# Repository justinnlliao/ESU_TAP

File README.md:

# ESU-TAP: Foot Pedal Interface (micro-ROS)

ESU-TAP is a research PCB interposer between an electrosurgical generator and its
footswitch. It logs pedal presses and lets a computer close the same footswitch
contacts over ROS 2, while the surgeon's pedal keeps working. It does not carry
the RF/patient output.

> **Research prototype. Not validated for clinical use.** Board-power loss is
> intended to fall back to the manual pedal, but this is not a verified fail-safe
> or emergency stop. Read [Safety and validation](docs/SAFETY.md)
> before connecting a generator, and test on a generator-disconnected fixture first.

## What you need

- An assembled ESU-TAP board ([hardware](hardware/README.md): v1, v2 or v3) with an ESP32-DevKitC
- Regulated 5 V DC, center-positive barrel supply for the relay rail; USB for the ESP32
- Ubuntu 22.04 with ROS 2 Humble and Docker (Docker runs only the micro-ROS agent)

## Quick start

```bash
git clone <this repo> && cd ESU_TAP
./esu.sh setup              # once: PlatformIO + ROS package; asks whether to pull the Docker agent
./esu.sh flash v3 pedal     # ESP32 plugged in, generator DISCONNECTED (v1/v2/v3; pedal or nopedal)
./esu.sh run                # agent + logger + commander in one tmux window
```

In the commander type `arm`, then `c`/`g`/`b`/`l` (cut/coag/bipolar/LigaSure),
`x` = all OFF and disarm, `q` = quit. `./esu.sh stop` stops everything.
`./esu.sh run v3 T01` also passes a trial ID to the logger.
`./esu.sh update` pulls, rebuilds and offers to reflash; `./esu.sh help` lists
everything. If `./esu.sh` says permission denied, use `bash esu.sh`.

- **pedal** (normal): boots in manual, with the pedal forwarded and logged.
  `/esu/arm` switches to autonomous (ROS drives the relays). Pressing any pedal
  cancels all computer commands and hands control back; re-arm to resume.
- **nopedal**: only for boards with nothing wired to the pedal inputs.

## Using ESU-TAP from your own ROS 2 nodes

Once flashed, only the micro-ROS agent has to run (`./esu.sh agent`). The board
then appears as ordinary services and a topic on `ROS_DOMAIN_ID` 0; no package
from this repository is needed.

| Interface | Type | Purpose |
| --- | --- | --- |
| `/esu/arm` | `std_srvs/srv/SetBool` | Enable/disable computer control (pedals always work) |
| `/esu/cut`, `/esu/coag`, `/esu/bipolar` | `std_srvs/srv/SetBool` | Set/clear a channel |
| `/esu/ligasure` | `std_srvs/srv/SetBool` | Set/clear LigaSure (v3 only) |
| `/esu/capabilities` | `std_srvs/srv/Trigger` | JSON: board, channels, firmware, armed state |
| `/esu/activation_state` | `std_msgs/msg/Int32` | Packed current state, published on change |

```bash
ros2 service call /esu/arm std_srvs/srv/SetBool "{data: true}"
ros2 service call /esu/cut std_srvs/srv/SetBool "{data: true}"
ros2 topic echo /esu/activation_state
```

A computer ON command expires after 500 ms: re-send ON about every 100 ms while
the channel should stay on. Only one node should send commands at a time.

`activation_state` bits 0-3 are CUT, COAG, bipolar, LigaSure; bits 4-5 are the
source: 0 pedal, 1 computer, 2 boot/reconnect baseline, 3 takeover (a pedal
press ended computer control; sent with the released computer channel, or with
the unchanged state when no computer output had to open).

To record data alongside your node, run `./esu.sh logger v3 <trial-id>`. It
writes `~/pedal_logs/pedal_log_<trial-id>_<time>.csv` plus a `.metadata.jsonl`.

### Package in another workspace

`software/ros2/src/pedal_controller` can be copied alone into another
workspace's `src/` and built with colcon; it depends only on `rclpy`,
`std_msgs` and `std_srvs`. From that workspace,
`bash src/pedal_controller/esu_run.sh v3` starts the agent, logger and commander.
See [setup](docs/SETUP.md#5-package-in-another-ros-2-workspace).

## How it works

Bypass relays route the pedal contacts to ESP32 inputs. The firmware closes
separate activation relays on the generator side when either a pedal is pressed
or an armed computer command is active. With board power off, the relays fall
back to connecting the pedal straight to the generator. Published state is
inferred from inputs and commands, not measured contact closure or RF delivery.

## Documentation

- [Setup guide](docs/SETUP.md): build, flash, run, logs
- [Safety and validation](docs/SAFETY.md): protections, known gaps, test record
- [Hardware](hardware/README.md) and [connectors](docs/CONNECTORS.md)
- [Changelog](CHANGELOG.md)

For contributors: [CONTRIBUTING.md](CONTRIBUTING.md) and
[docs/contributors/](docs/contributors/README.md) (testing, roadmap, firmware
internals, hardware proposals, enclosure).

## License

[Apache 2.0](LICENSE).

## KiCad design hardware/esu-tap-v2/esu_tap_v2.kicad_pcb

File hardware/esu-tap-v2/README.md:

# ESU-TAP v2

Six-relay, three-channel (CUT, COAG, bipolar) design. Open `esu_tap_v2.kicad_pro`.
Build firmware with `--board v2`.

One v2 board passed a disconnected-fixture bench session on 2026-10-22; see the
[test record](../../docs/SAFETY.md#recorded-v2-disconnected-fixture-test-2026-10-22).
U9 RESET drives Q1 (bypass relays only) and ESP32 EN is unconnected, so the
watchdog does not reset the ESP32 or clear activation outputs.

Enclosure dimensions: [contributors/ENCLOSURE_V2.md](../../docs/contributors/ENCLOSURE_V2.md).
The v3 reference designators in
[HARDWARE_FAULT_HANDLING.md](../../docs/contributors/HARDWARE_FAULT_HANDLING.md)
do not apply directly to v2.

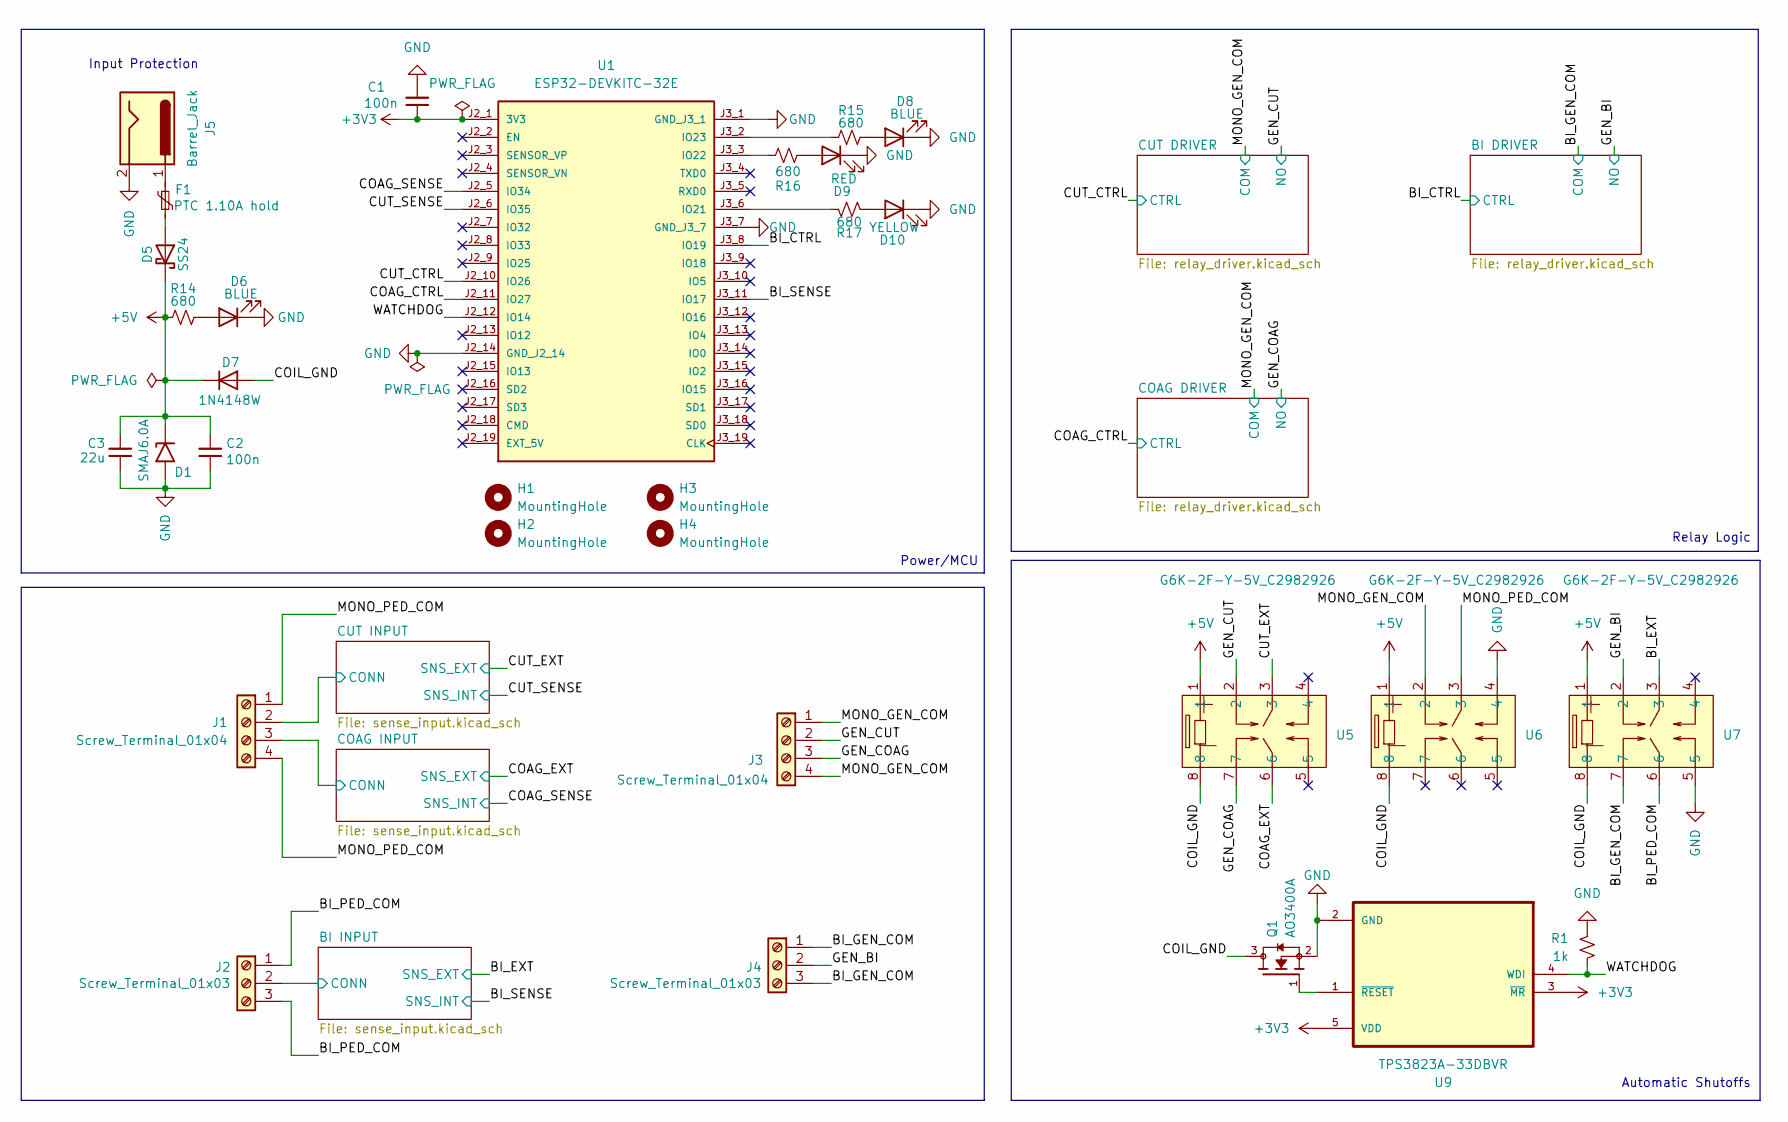
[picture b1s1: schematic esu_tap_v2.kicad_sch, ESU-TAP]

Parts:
C1: 100n; C_0402_1005Metric_Pad0.74x0.62mm_HandSolder; LCSC C1525
C2: 100n; C_0805_2012Metric_Pad1.18x1.45mm_HandSolder; LCSC C49678
C3: 22u; C_0805_2012Metric_Pad1.18x1.45mm_HandSolder; LCSC C296720
D1: SMAJ6.0A; D_SMA; LCSC C364284
D5: SS24; D_SMA; LCSC C115726
D6, D8: BLUE; LED_0603_1608Metric_Pad1.05x0.95mm_HandSolder; LCSC C2288
D7: 1N4148W; D_SOD-123; LCSC C81598
D9: RED; LED_0603_1608Metric_Pad1.05x0.95mm_HandSolder; LCSC C2286
D10: YELLOW; LED_0603_1608Metric_Pad1.05x0.95mm_HandSolder; LCSC C2287
F1: PTC 1.10A hold; Fuse_1812_4532Metric; MPN 1812L110/16DR; LCSC C142746
H1, H2, H3, H4: MountingHole; MountingHole_3.2mm_M3_DIN965
J1, J3: Screw_Terminal_01x04; TerminalBlock_Phoenix_MKDS-1,5-4-5.08_1x04_P5.08mm_Horizont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
J2, J4: Screw_Terminal_01x03; TerminalBlock_Phoenix_MKDS-1,5-3-5.08_1x03_P5.08mm_Horizont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
J5: Barrel_Jack; BarrelJack_CUI_PJ-102AH_Horizontal
Q1: AO3400A; SOT95P280X125-3N; PARTREV L; LCSC C20917
R1: 1k; R_0402_1005Metric_Pad0.72x0.64mm_HandSolder; LCSC C11702
R14, R15, R16, R17: 680; R_0402_1005Metric_Pad0.72x0.64mm_HandSolder; LCSC C137948
U1: ESP32-DEVKITC-32E; MODULE_ESP32-DEVKITC-32E; PARTREV 1.4
U5, U6, U7: G6K-2F-Y-5V_C2982926; RELAY-SMD_G6K-2F-Y; MPN G6K-2F-Y-5V; LCSC C2982926
U9: TPS3823A-33DBVR; SOT95P280X145-5N; LCSC C702191

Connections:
+3V3: C1.1, U1.J2_1 (3V3), U9.3 (~MR), U9.5 (VDD); also elsewhere on the board
+5V: C2.2, C3.2, D1.1 (A1), D5.1 (K), D7.1 (K), R14.1, U5.1, U6.1, U7.1; also elsewhere on the board
/BI_CTRL: U1.J3_8 (IO19); also elsewhere on the board
/BI_EXT: J2.2, U7.3; also elsewhere on the board
/BI_GEN_COM: J4.1, J4.3, U7.7; also elsewhere on the board
/BI_PED_COM: J2.1, J2.3, U7.6
/BI_SENSE: U1.J3_11 (IO17); also elsewhere on the board
/COAG_CTRL: U1.J2_11 (IO27); also elsewhere on the board
/COAG_EXT: J1.3, U5.6; also elsewhere on the board
/COAG_SENSE: U1.J2_5 (IO34); also elsewhere on the board
/COIL_GND: D7.2 (A), Q1.3, U5.8, U6.8, U7.8
/CUT_CTRL: U1.J2_10 (IO26); also elsewhere on the board
/CUT_EXT: J1.2, U5.3; also elsewhere on the board
/CUT_SENSE: U1.J2_6 (IO35); also elsewhere on the board
/GEN_BI: J4.2, U7.2; also elsewhere on the board
/GEN_COAG: J3.3, U5.7; also elsewhere on the board
/GEN_CUT: J3.2, U5.2; also elsewhere on the board
/MONO_GEN_COM: J3.1, J3.4, U6.2; also elsewhere on the board
/MONO_PED_COM: J1.1, J1.4, U6.3
/WATCHDOG: R1.1, U1.J2_12 (IO14), U9.4 (WDI)
GND: C1.2, C2.1, C3.1, D1.2 (A2), D6.1 (K), D8.1 (K), D9.1 (K), D10.1 (K), J5.2, Q1.2, R1.2, U1.J2_14 (GND_J2_14), U1.J3_1 (GND_J3_1), U1.J3_7 (GND_J3_7), U6.4, U7.5, U9.2 (GND); also elsewhere on the board
unnamed: D5.2 (A), F1.2
unnamed: D6.2 (A), R14.2
unnamed: D8.2 (A), R15.2
unnamed: D9.2 (A), R16.2
unnamed: D10.2 (A), R17.2
unnamed: F1.1, J5.1
unnamed: R17.1, U1.J3_6 (IO21)
unnamed: R16.1, U1.J3_3 (IO22)
unnamed: R15.1, U1.J3_2 (IO23)
unnamed: Q1.1, U9.1 (~RESET)

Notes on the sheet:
Input Protection
Automatic Shutoffs
Relay Logic
Power/MCU

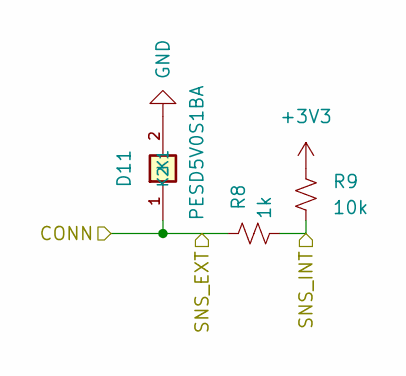
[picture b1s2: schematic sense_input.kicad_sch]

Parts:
D11: PESD5V0S1BA; SOD2613X115N; LCSC C19224
R8: 1k; R_0402_1005Metric_Pad0.72x0.64mm_HandSolder; LCSC C11702
R9: 10k; R_0402_1005Metric_Pad0.72x0.64mm_HandSolder; LCSC C60490

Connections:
+3V3: R9.1; also elsewhere on the board
/CUT_EXT: D11.1 (K1), R8.1; also elsewhere on the board
/CUT_SENSE: R8.2, R9.2; also elsewhere on the board
GND: D11.2 (K2); also elsewhere on the board

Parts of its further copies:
D14, D15: PESD5V0S1BA; SOD2613X115N; LCSC C19224
R10, R12: 1k; R_0402_1005Metric_Pad0.72x0.64mm_HandSolder; LCSC C11702
R11, R13: 10k; R_0402_1005Metric_Pad0.72x0.64mm_HandSolder; LCSC C60490

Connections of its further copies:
+3V3: R11.1, R13.1; also elsewhere on the board
/BI_EXT: D15.1 (K1), R12.1; also elsewhere on the board
/BI_SENSE: R12.2, R13.2; also elsewhere on the board
/COAG_EXT: D14.1 (K1), R10.1; also elsewhere on the board
/COAG_SENSE: R10.2, R11.2; also elsewhere on the board
GND: D14.2 (K2), D15.2 (K2); also elsewhere on the board

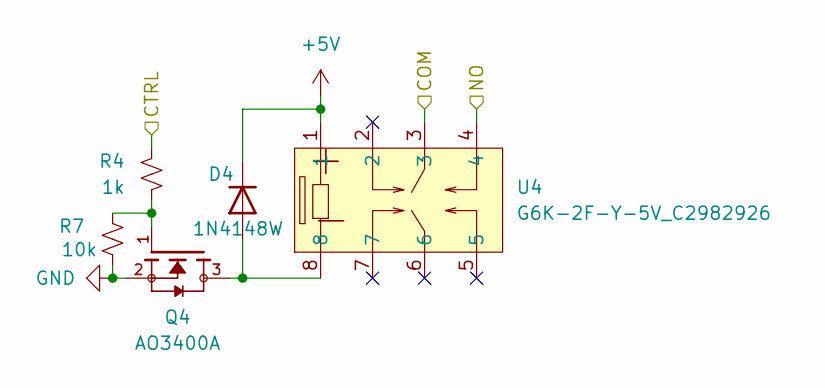
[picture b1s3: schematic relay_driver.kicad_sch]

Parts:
D4: 1N4148W; D_SOD-123; LCSC C81598
Q4: AO3400A; SOT95P280X125-3N; PARTREV L; LCSC C20917
R4: 1k; R_0402_1005Metric_Pad0.72x0.64mm_HandSolder; LCSC C11702
R7: 10k; R_0402_1005Metric_Pad0.72x0.64mm_HandSolder; LCSC C60490
U4: G6K-2F-Y-5V_C2982926; RELAY-SMD_G6K-2F-Y; MPN G6K-2F-Y-5V; LCSC C2982926

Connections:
+5V: D4.1 (K), U4.1; also elsewhere on the board
/BI_CTRL: R4.2; also elsewhere on the board
/BI_GEN_COM: U4.3; also elsewhere on the board
/GEN_BI: U4.4; also elsewhere on the board
GND: Q4.2, R7.1; also elsewhere on the board
unnamed: D4.2 (A), Q4.3, U4.8
unnamed: Q4.1, R4.1, R7.2

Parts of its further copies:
D2, D3: 1N4148W; D_SOD-123; LCSC C81598
Q2, Q3: AO3400A; SOT95P280X125-3N; PARTREV L; LCSC C20917
R2, R3: 1k; R_0402_1005Metric_Pad0.72x0.64mm_HandSolder; LCSC C11702
R5, R6: 10k; R_0402_1005Metric_Pad0.72x0.64mm_HandSolder; LCSC C60490
U2, U3: G6K-2F-Y-5V_C2982926; RELAY-SMD_G6K-2F-Y; MPN G6K-2F-Y-5V; LCSC C2982926

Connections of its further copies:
+5V: D2.1 (K), D3.1 (K), U2.1, U3.1; also elsewhere on the board
/COAG_CTRL: R3.2; also elsewhere on the board
/CUT_CTRL: R2.2; also elsewhere on the board
/GEN_COAG: U3.4; also elsewhere on the board
/GEN_CUT: U2.4; also elsewhere on the board
/MONO_GEN_COM: U2.3, U3.3; also elsewhere on the board
GND: Q2.2, Q3.2, R5.1, R6.1; also elsewhere on the board
unnamed: D2.2 (A), Q2.3, U2.8
unnamed: D3.2 (A), Q3.3, U3.8
unnamed: Q2.1, R2.1, R5.2
unnamed: Q3.1, R3.1, R6.2

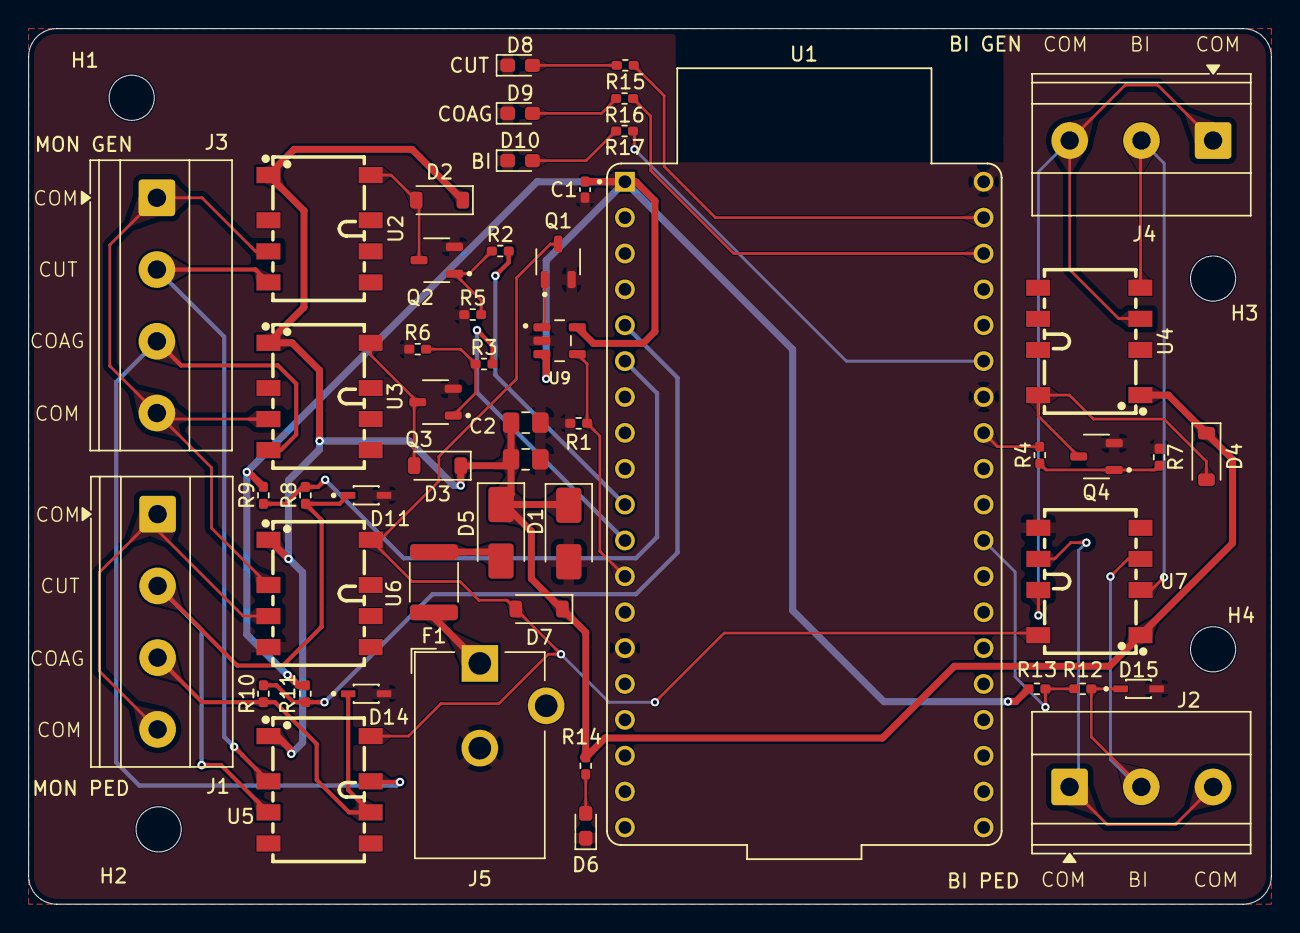
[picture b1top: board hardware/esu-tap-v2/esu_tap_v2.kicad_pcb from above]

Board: 2 copper layers, 88.0 x 62.0 mm, 55 parts (0 on the bottom side), 37 nets.

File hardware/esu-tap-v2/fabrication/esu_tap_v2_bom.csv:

Comment,Designator,Footprint,LCSC Part #
100n,C1,C_0402_1005Metric,C1525
100n,C2,C_0805_2012Metric,C49678
22u,C3,C_0805_2012Metric,C296720
SMAJ6.0A,D1,SMA,C364284
1N4148W,D2,SOD-123,C81598
1N4148W,D3,SOD-123,C81598
1N4148W,D4,SOD-123,C81598
SS24,D5,SMA,C115726
BLUE,D6,LED_0603_1608Metric,C2288
1N4148W,D7,SOD-123,C81598
BLUE,D8,LED_0603_1608Metric,C2288
RED,D9,LED_0603_1608Metric,C2286
YELLOW,D10,LED_0603_1608Metric,C2287
PESD5V0S1BA,D11,SOD-323,C19224
PESD5V0S1BA,D14,SOD-323,C19224
PESD5V0S1BA,D15,SOD-323,C19224
PTC 1.10A hold,F1,Fuse_1812_4532Metric,C142746
AO3400A,Q1,SOT-23,C20917
AO3400A,Q2,SOT-23,C20917
AO3400A,Q3,SOT-23,C20917
AO3400A,Q4,SOT-23,C20917
1k,R1,R_0402_1005Metric,C11702
1k,R2,R_0402_1005Metric,C11702
1k,R3,R_0402_1005Metric,C11702
1k,R4,R_0402_1005Metric,C11702
10k,R5,R_0402_1005Metric,C60490
10k,R6,R_0402_1005Metric,C60490
10k,R7,R_0402_1005Metric,C60490
1k,R8,R_0402_1005Metric,C11702
10k,R9,R_0402_1005Metric,C60490
1k,R10,R_0402_1005Metric,C11702
10k,R11,R_0402_1005Metric,C60490
1k,R12,R_0402_1005Metric,C11702
10k,R13,R_0402_1005Metric,C60490
680,R14,R_0402_1005Metric,C137948
680,R15,R_0402_1005Metric,C137948
680,R16,R_0402_1005Metric,C137948
680,R17,R_0402_1005Metric,C137948
G6K-2F-Y-5V_C2982926,U2,RELAY-SMD_G6K-2F-Y,C2982926
G6K-2F-Y-5V_C2982926,U3,RELAY-SMD_G6K-2F-Y,C2982926
G6K-2F-Y-5V_C2982926,U4,RELAY-SMD_G6K-2F-Y,C2982926
G6K-2F-Y-5V_C2982926,U5,RELAY-SMD_G6K-2F-Y,C2982926
G6K-2F-Y-5V_C2982926,U6,RELAY-SMD_G6K-2F-Y,C2982926
G6K-2F-Y-5V_C2982926,U7,RELAY-SMD_G6K-2F-Y,C2982926
TPS3823A-33DBVR,U9,SOT-23-5,C702191

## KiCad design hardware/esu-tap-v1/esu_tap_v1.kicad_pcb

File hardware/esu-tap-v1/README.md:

# ESU-TAP v1

Original two-channel (CUT, COAG) design, kept for existing boards. Open
`esu_tap_v1.kicad_pro`. New work is in [v3](../esu-tap-v3/README.md).

Build firmware with `--board v1`: v1 uses sense GPIO34/35 and LED GPIO18/21, so a
v2/v3 profile must not be flashed onto it. v1 has no external watchdog. No
physical test of a v1 board with the current firmware is recorded.

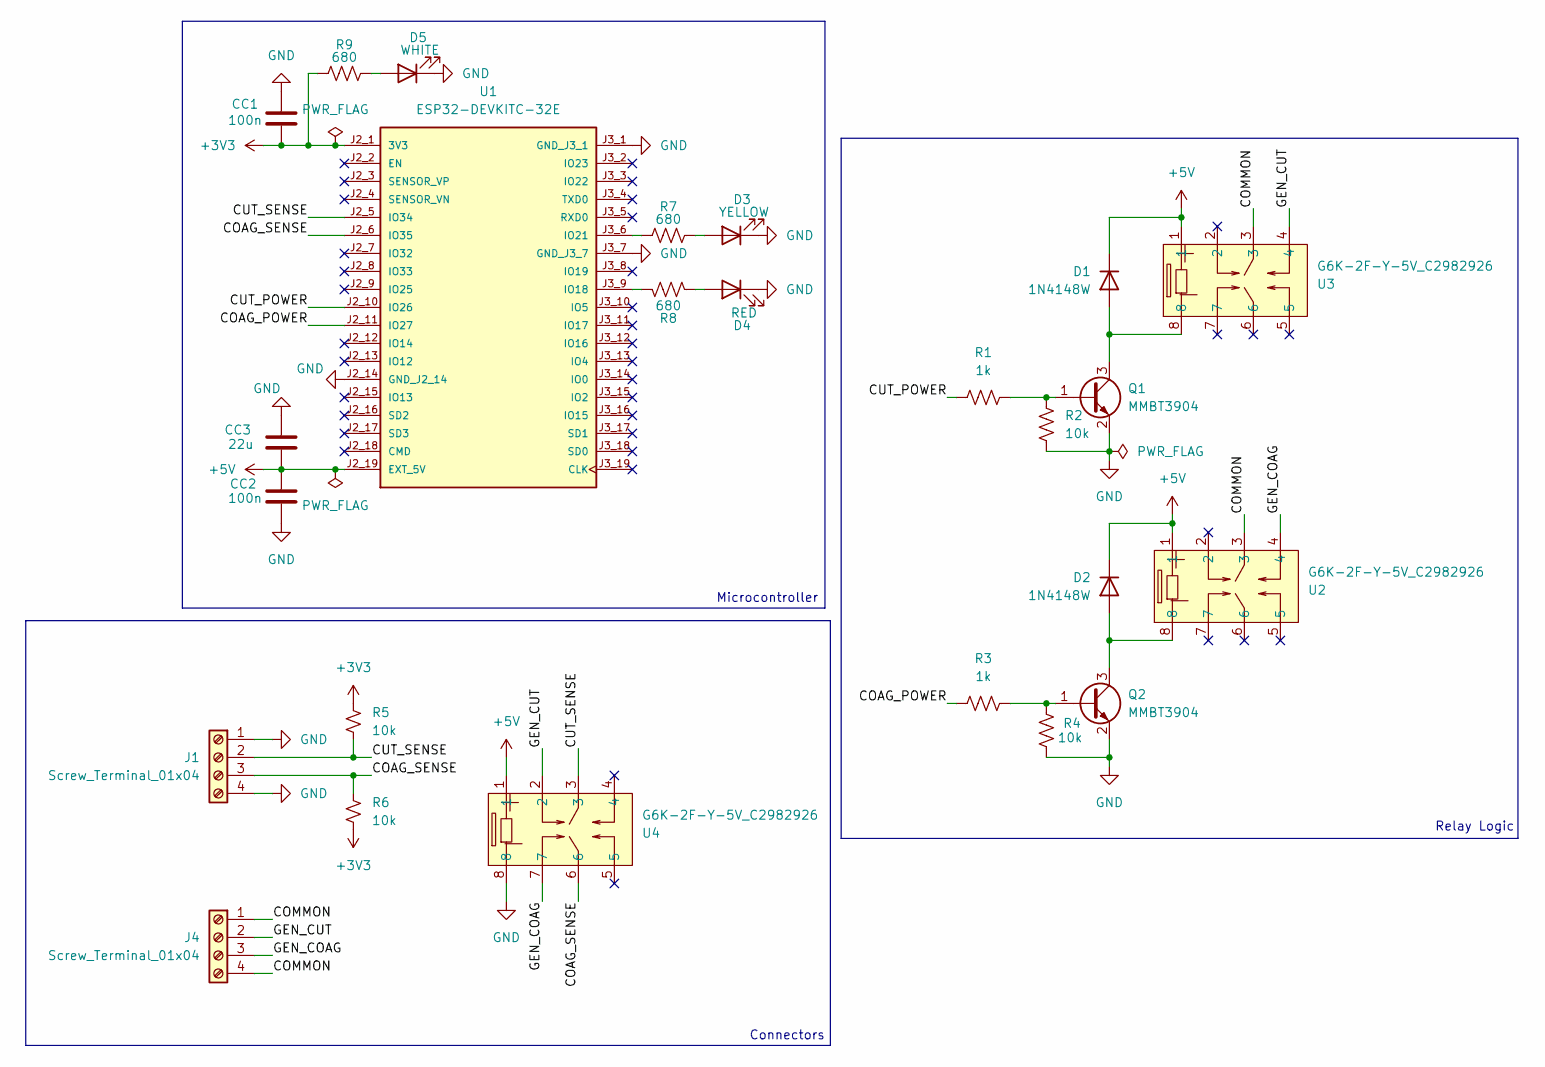
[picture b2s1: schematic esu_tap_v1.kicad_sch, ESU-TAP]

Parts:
CC1, CC2: 100n; C_0402_1005Metric_Pad0.74x0.62mm_HandSolder; LCSC C1525
CC3: 22u; C_0402_1005Metric_Pad0.74x0.62mm_HandSolder; LCSC C22367823
D1, D2: 1N4148W; D_SOD-123; LCSC C81598
D3: YELLOW; LED_0603_1608Metric_Pad1.05x0.95mm_HandSolder; LCSC C2287
D4: RED; LED_0603_1608Metric_Pad1.05x0.95mm_HandSolder; LCSC C2286
D5: WHITE; LED_0603_1608Metric_Pad1.05x0.95mm_HandSolder; LCSC C2290
J1, J4: Screw_Terminal_01x04; TerminalBlock_Phoenix_MKDS-1,5-4-5.08_1x04_P5.08mm_Horizont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
Q1, Q2: MMBT3904; SOT-23; LCSC C20526
R1, R3: 1k; R_0402_1005Metric_Pad0.72x0.64mm_HandSolder; LCSC C11702
R2, R4, R5, R6: 10k; R_0402_1005Metric_Pad0.72x0.64mm_HandSolder; LCSC C2889342
R7, R8, R9: 680; R_0402_1005Metric_Pad0.72x0.64mm_HandSolder; LCSC C25130
U1: ESP32-DEVKITC-32E; MODULE_ESP32-DEVKITC-32E; PARTREV 1.4
U2, U3, U4: G6K-2F-Y-5V_C2982926; RELAY-SMD_G6K-2F-Y; MPN G6K-2F-Y-5V; LCSC C2982926

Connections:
+3V3: CC1.1, R5.1, R6.2, R9.1, U1.J2_1 (3V3)
+5V: CC2.2, CC3.1, D1.1 (K), D2.1 (K), U1.J2_19 (EXT_5V), U2.1, U3.1, U4.1
/COAG_POWER: R3.1, U1.J2_11 (IO27)
/COAG_SENSE: J1.3, R6.1, U1.J2_6 (IO35), U4.6
/COMMON: J4.1, J4.4, U2.3, U3.3
/CUT_POWER: R1.1, U1.J2_10 (IO26)
/CUT_SENSE: J1.2, R5.2, U1.J2_5 (IO34), U4.3
/GEN_COAG: J4.3, U2.4, U4.7
/GEN_CUT: J4.2, U3.4, U4.2
GND: CC1.2, CC2.1, CC3.2, D3.1 (K), D4.1 (K), D5.1 (K), J1.1, J1.4, Q1.2 (E), Q2.2 (E), R2.1, R4.1, U1.J2_14 (GND_J2_14), U1.J3_1 (GND_J3_1), U1.J3_7 (GND_J3_7), U4.8
unnamed: D1.2 (A), Q1.3 (C), U3.8
unnamed: D2.2 (A), Q2.3 (C), U2.8
unnamed: D3.2 (A), R7.2
unnamed: D4.2 (A), R8.2
unnamed: D5.2 (A), R9.2
unnamed: Q1.1 (B), R1.2, R2.2
unnamed: Q2.1 (B), R3.2, R4.2
unnamed: R8.1, U1.J3_9 (IO18)
unnamed: R7.1, U1.J3_6 (IO21)

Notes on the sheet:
Connectors
Relay Logic
Microcontroller

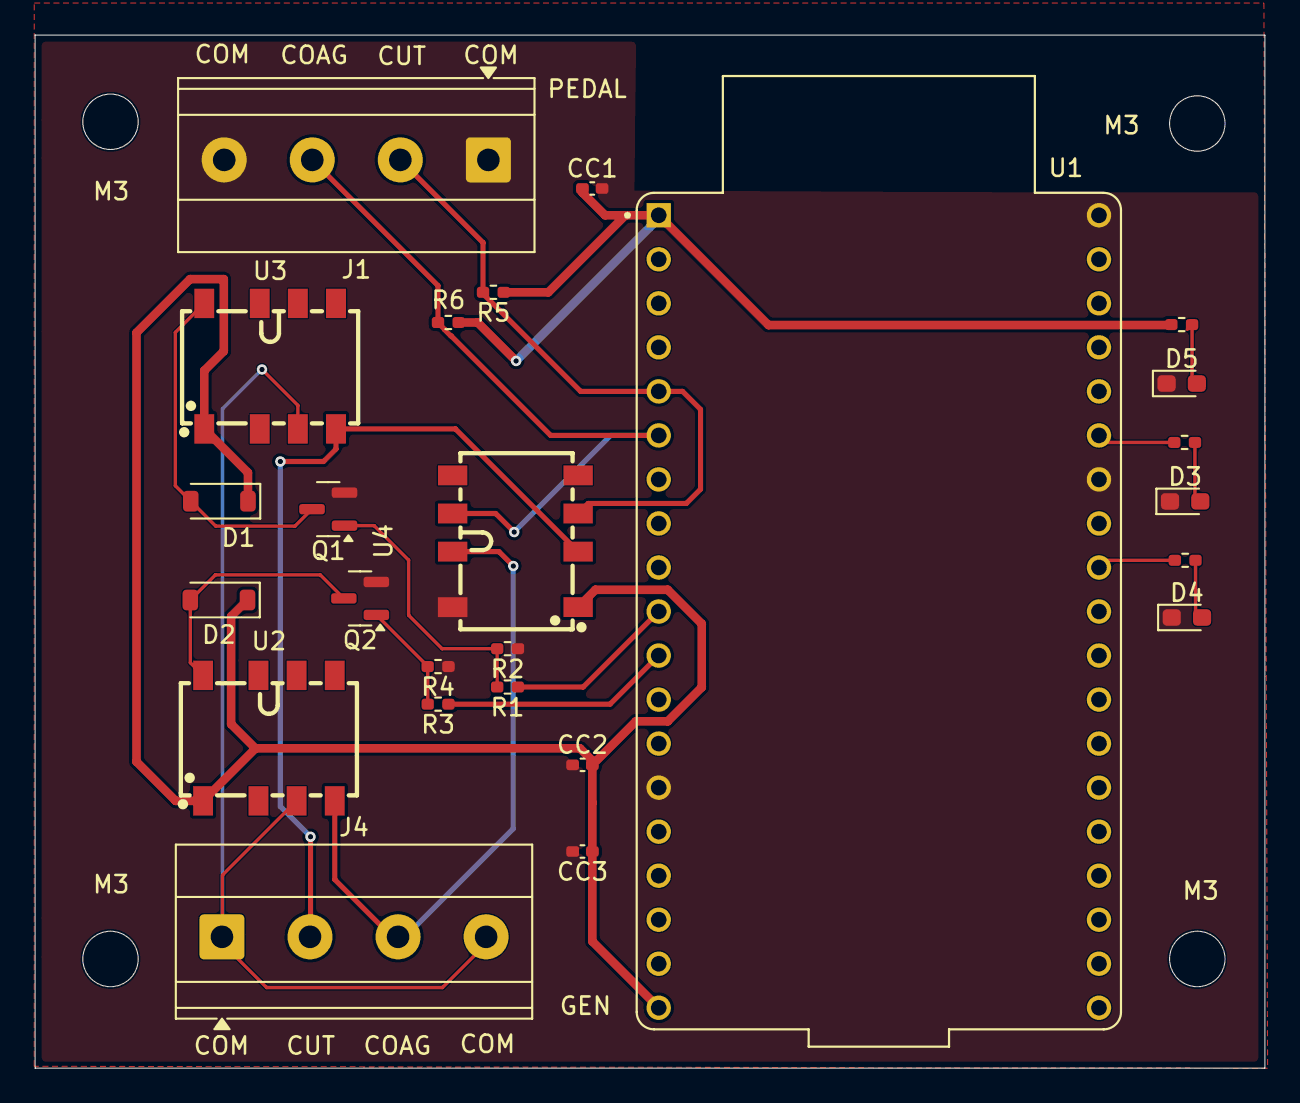
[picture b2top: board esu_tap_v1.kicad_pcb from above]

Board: 2 copper layers, 70.9 x 59.6 mm, 29 parts (0 on the bottom side), 19 nets.

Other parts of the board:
M3, M3#2, M3#3, M3#4: MountingHole_3.2mm_M3_DIN965

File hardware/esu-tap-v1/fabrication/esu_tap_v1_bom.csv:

"Comment","Designator","Footprint","LCSC Part #"
"100n","CC1,CC2","Capacitor_SMD:C_0402_1005Metric_Pad0.74x0.62mm_HandSolder","C1525"
"22u","CC3","Capacitor_SMD:C_0402_1005Metric_Pad0.74x0.62mm_HandSolder","C22367823"
"1N4148W","D1,D2","Diode_SMD:D_SOD-123","C81598"
"YELLOW","D3","LED_SMD:LED_0603_1608Metric_Pad1.05x0.95mm_HandSolder","C2287"
"RED","D4","LED_SMD:LED_0603_1608Metric_Pad1.05x0.95mm_HandSolder","C2286"
"WHITE","D5","LED_SMD:LED_0603_1608Metric_Pad1.05x0.95mm_HandSolder","C2290"
"MMBT3904","Q1,Q2","Package_TO_SOT_SMD:SOT-23","C20526"
"1k","R1,R3","Resistor_SMD:R_0402_1005Metric_Pad0.72x0.64mm_HandSolder","C11702"
"10k","R2,R4,R5,R6","Resistor_SMD:R_0402_1005Metric_Pad0.72x0.64mm_HandSolder","C2889342"
"680","R7,R8,R9","Resistor_SMD:R_0402_1005Metric_Pad0.72x0.64mm_HandSolder","C25130"
"G6K-2F-Y-5V_C2982926","U2,U3,U4","G6K-2F-Y:RELAY-SMD_G6K-2F-Y","C2982926"

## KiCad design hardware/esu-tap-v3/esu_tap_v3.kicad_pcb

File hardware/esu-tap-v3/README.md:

# ESU-TAP v3

Latest design: eight relays, four channels (CUT, COAG, bipolar, and a path
labeled LigaSure). Open `esu_tap_v3.kicad_pro` in KiCad 10 (checked with 10.0.5).
Build firmware with `--board v3`.

LigaSure uses GPIO33 control, GPIO25 sense, and GPIO18 through R22 (680 ohm) to
yellow indicator D12. The schematic note "GPIO32" is stale. No physical test of
a v3 board is recorded yet, and LigaSure compatibility with a specific
vessel-sealing generator is not established.

U10 RESET drives Q1, which controls bypass relays U6-U9 only. It does not reset
the ESP32 or disable activation relays U2-U5; see [SAFETY.md](../../docs/SAFETY.md)
and the proposed fixes in
[HARDWARE_FAULT_HANDLING.md](../../docs/contributors/HARDWARE_FAULT_HANDLING.md).

## Manufacturing files

`fabrication/` holds the BOM, CPL and job file. The CPL uses
`Designator,Mid X,Mid Y,Rotation,Layer`: mm, counterclockwise degrees 0-359,
Top/Bottom. Part-specific JLC rotation corrections are not applied; check every
polarized part in JLCPCB's preview.

The 2026-09-11 KiCad review reported no ERC/DRC errors, no unconnected items and
no schematic/PCB parity issues under the configured checks, with nine footprint
library and five schematic warnings remaining. Some rule checks are disabled.

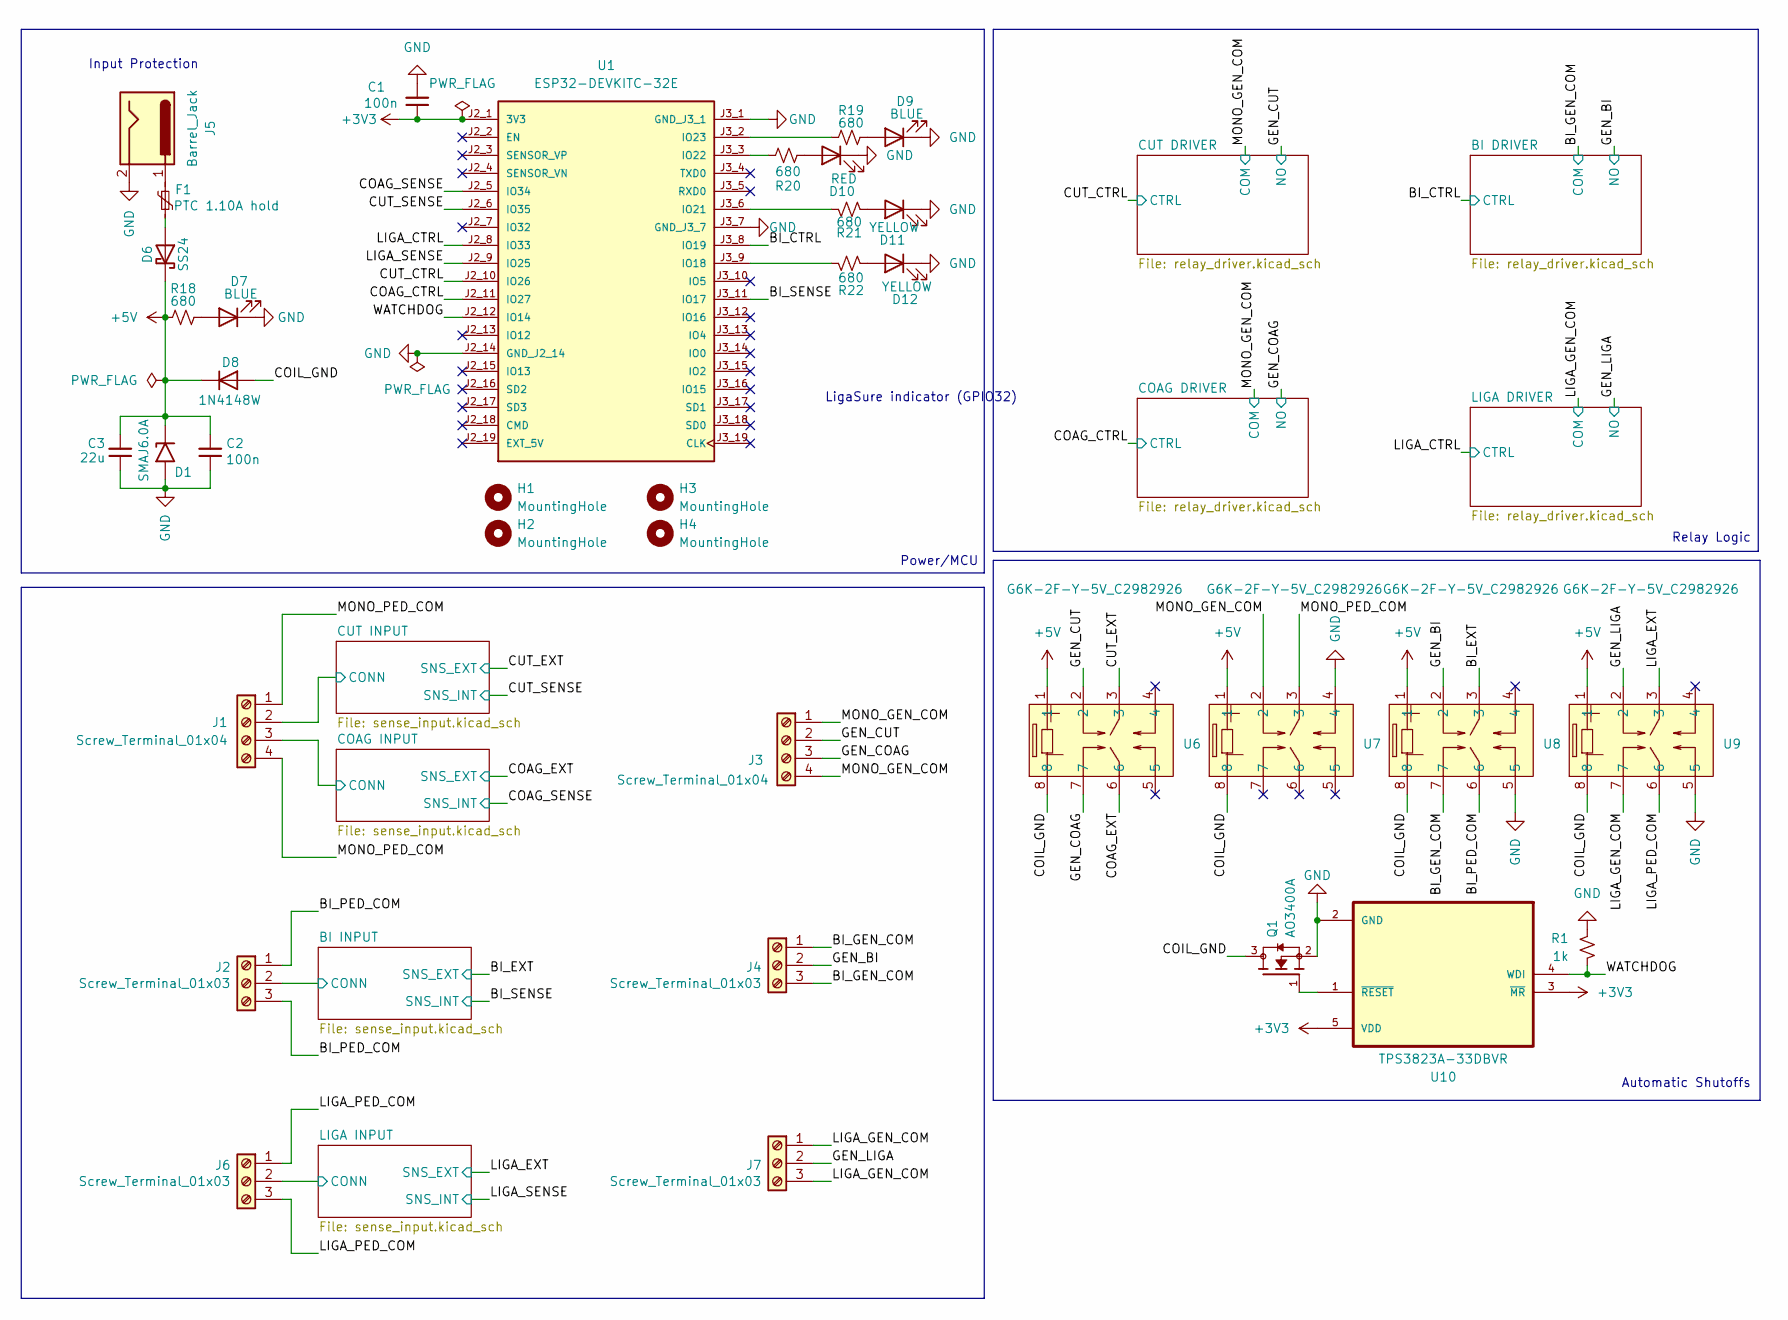
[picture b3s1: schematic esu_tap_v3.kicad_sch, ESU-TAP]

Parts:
C1: 100n; C_0402_1005Metric_Pad0.74x0.62mm_HandSolder; LCSC C1525
C2: 100n; C_0805_2012Metric_Pad1.18x1.45mm_HandSolder; LCSC C49678
C3: 22u; C_0805_2012Metric_Pad1.18x1.45mm_HandSolder; LCSC C296720
D1: SMAJ6.0A; D_SMA; LCSC C364284
D6: SS24; D_SMA; LCSC C115726
D7, D9: BLUE; LED_0603_1608Metric_Pad1.05x0.95mm_HandSolder; LCSC C2288
D8: 1N4148W; D_SOD-123; LCSC C81598
D10: RED; LED_0603_1608Metric_Pad1.05x0.95mm_HandSolder; LCSC C2286
D11, D12: YELLOW; LED_0603_1608Metric_Pad1.05x0.95mm_HandSolder; LCSC C2287
F1: PTC 1.10A hold; Fuse_1812_4532Metric; MPN 1812L110/16DR; LCSC C142746
H1, H2, H3, H4: MountingHole; MountingHole_3.2mm_M3_DIN965
J1, J3: Screw_Terminal_01x04; TerminalBlock_Phoenix_MKDS-1,5-4-5.08_1x04_P5.08mm_Horizont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
J2, J4, J6, J7: Screw_Terminal_01x03; TerminalBlock_Phoenix_MKDS-1,5-3-5.08_1x03_P5.08mm_Horizont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
J5: Barrel_Jack; BarrelJack_CUI_PJ-102AH_Horizontal
Q1: AO3400A; SOT95P280X125-3N; PARTREV L; LCSC C20917
R1: 1k; R_0402_1005Metric_Pad0.72x0.64mm_HandSolder; LCSC C11702
R18, R19, R20, R21, R22: 680; R_0402_1005Metric_Pad0.72x0.64mm_HandSolder; LCSC C137948
U1: ESP32-DEVKITC-32E; MODULE_ESP32-DEVKITC-32E; PARTREV 1.4
U6, U7, U8, U9: G6K-2F-Y-5V_C2982926; RELAY-SMD_G6K-2F-Y; MPN G6K-2F-Y-5V; LCSC C2982926
U10: TPS3823A-33DBVR; SOT95P280X145-5N; LCSC C702191

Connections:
+3V3: C1.1, U1.J2_1 (3V3), U10.3 (~MR), U10.5 (VDD); also elsewhere on the board
+5V: C2.2, C3.2, D1.1 (A1), D6.1 (K), D8.1 (K), R18.1, U6.1, U7.1, U8.1, U9.1; also elsewhere on the board
/BI_CTRL: U1.J3_8 (IO19); also elsewhere on the board
/BI_EXT: J2.2, U8.3; also elsewhere on the board
/BI_GEN_COM: J4.1, J4.3, U8.7; also elsewhere on the board
/BI_PED_COM: J2.1, J2.3, U8.6
/BI_SENSE: U1.J3_11 (IO17); also elsewhere on the board
/COAG_CTRL: U1.J2_11 (IO27); also elsewhere on the board
/COAG_EXT: J1.3, U6.6; also elsewhere on the board
/COAG_SENSE: U1.J2_5 (IO34); also elsewhere on the board
/COIL_GND: D8.2 (A), Q1.3, U6.8, U7.8, U8.8, U9.8
/CUT_CTRL: U1.J2_10 (IO26); also elsewhere on the board
/CUT_EXT: J1.2, U6.3; also elsewhere on the board
/CUT_SENSE: U1.J2_6 (IO35); also elsewhere on the board
/GEN_BI: J4.2, U8.2; also elsewhere on the board
/GEN_COAG: J3.3, U6.7; also elsewhere on the board
/GEN_CUT: J3.2, U6.2; also elsewhere on the board
/GEN_LIGA: J7.2, U9.2; also elsewhere on the board
/LIGA_CTRL: U1.J2_8 (IO33); also elsewhere on the board
/LIGA_EXT: J6.2, U9.3; also elsewhere on the board
/LIGA_GEN_COM: J7.1, J7.3, U9.7; also elsewhere on the board
/LIGA_PED_COM: J6.1, J6.3, U9.6
/LIGA_SENSE: U1.J2_9 (IO25); also elsewhere on the board
/MONO_GEN_COM: J3.1, J3.4, U7.2; also elsewhere on the board
/MONO_PED_COM: J1.1, J1.4, U7.3
/WATCHDOG: R1.1, U1.J2_12 (IO14), U10.4 (WDI)
GND: C1.2, C2.1, C3.1, D1.2 (A2), D7.1 (K), D9.1 (K), D10.1 (K), D11.1 (K), D12.1 (K), J5.2, Q1.2, R1.2, U1.J2_14 (GND_J2_14), U1.J3_1 (GND_J3_1), U1.J3_7 (GND_J3_7), U7.4, U8.5, U9.5, U10.2 (GND); also elsewhere on the board
unnamed: D6.2 (A), F1.2
unnamed: D7.2 (A), R18.2
unnamed: D9.2 (A), R19.2
unnamed: D10.2 (A), R20.2
unnamed: D11.2 (A), R21.2
unnamed: D12.2 (A), R22.2
unnamed: F1.1, J5.1
unnamed: R22.1, U1.J3_9 (IO18)
unnamed: R21.1, U1.J3_6 (IO21)
unnamed: R20.1, U1.J3_3 (IO22)
unnamed: R19.1, U1.J3_2 (IO23)
unnamed: Q1.1, U10.1 (~RESET)

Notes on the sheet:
LigaSure indicator (GPIO32)
Input Protection
Automatic Shutoffs
Relay Logic
Power/MCU

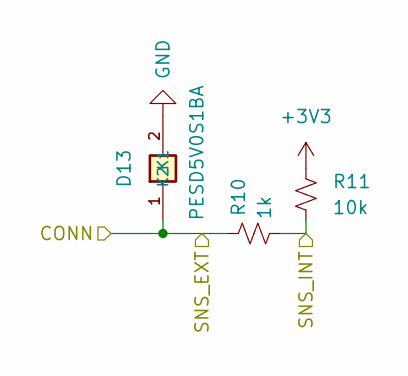
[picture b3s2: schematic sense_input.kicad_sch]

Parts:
D13: PESD5V0S1BA; SOD2613X115N; LCSC C19224
R10: 1k; R_0402_1005Metric_Pad0.72x0.64mm_HandSolder; LCSC C11702
R11: 10k; R_0402_1005Metric_Pad0.72x0.64mm_HandSolder; LCSC C60490

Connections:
+3V3: R11.1; also elsewhere on the board
/CUT_EXT: D13.1 (K1), R10.1; also elsewhere on the board
/CUT_SENSE: R10.2, R11.2; also elsewhere on the board
GND: D13.2 (K2); also elsewhere on the board

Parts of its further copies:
D14, D15, D16: PESD5V0S1BA; SOD2613X115N; LCSC C19224
R12, R14, R16: 1k; R_0402_1005Metric_Pad0.72x0.64mm_HandSolder; LCSC C11702
R13, R15, R17: 10k; R_0402_1005Metric_Pad0.72x0.64mm_HandSolder; LCSC C60490

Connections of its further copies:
+3V3: R13.1, R15.1, R17.1; also elsewhere on the board
/BI_EXT: D15.1 (K1), R14.1; also elsewhere on the board
/BI_SENSE: R14.2, R15.2; also elsewhere on the board
/COAG_EXT: D14.1 (K1), R12.1; also elsewhere on the board
/COAG_SENSE: R12.2, R13.2; also elsewhere on the board
/LIGA_EXT: D16.1 (K1), R16.1; also elsewhere on the board
/LIGA_SENSE: R16.2, R17.2; also elsewhere on the board
GND: D14.2 (K2), D15.2 (K2), D16.2 (K2); also elsewhere on the board

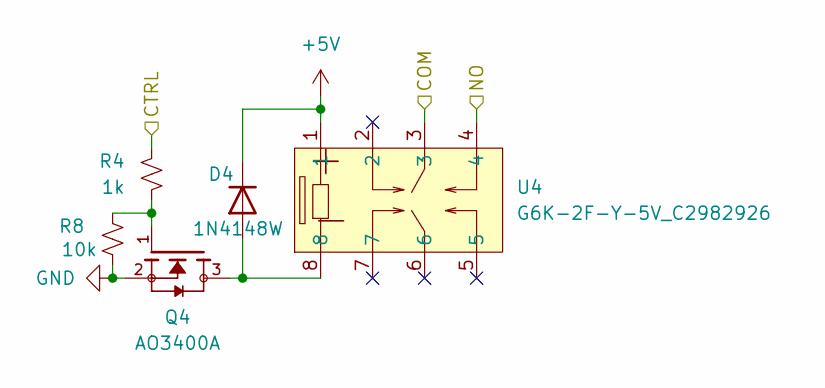
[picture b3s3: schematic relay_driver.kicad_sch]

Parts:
D4: 1N4148W; D_SOD-123; LCSC C81598
Q4: AO3400A; SOT95P280X125-3N; PARTREV L; LCSC C20917
R4: 1k; R_0402_1005Metric_Pad0.72x0.64mm_HandSolder; LCSC C11702
R8: 10k; R_0402_1005Metric_Pad0.72x0.64mm_HandSolder; LCSC C60490
U4: G6K-2F-Y-5V_C2982926; RELAY-SMD_G6K-2F-Y; MPN G6K-2F-Y-5V; LCSC C2982926

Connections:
+5V: D4.1 (K), U4.1; also elsewhere on the board
/BI_CTRL: R4.2; also elsewhere on the board
/BI_GEN_COM: U4.3; also elsewhere on the board
/GEN_BI: U4.4; also elsewhere on the board
GND: Q4.2, R8.1; also elsewhere on the board
unnamed: D4.2 (A), Q4.3, U4.8
unnamed: Q4.1, R4.1, R8.2

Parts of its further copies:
D2, D3, D5: 1N4148W; D_SOD-123; LCSC C81598
Q2, Q3, Q5: AO3400A; SOT95P280X125-3N; PARTREV L; LCSC C20917
R2, R3, R5: 1k; R_0402_1005Metric_Pad0.72x0.64mm_HandSolder; LCSC C11702
R6, R7, R9: 10k; R_0402_1005Metric_Pad0.72x0.64mm_HandSolder; LCSC C60490
U2, U3, U5: G6K-2F-Y-5V_C2982926; RELAY-SMD_G6K-2F-Y; MPN G6K-2F-Y-5V; LCSC C2982926

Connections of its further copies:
+5V: D2.1 (K), D3.1 (K), D5.1 (K), U2.1, U3.1, U5.1; also elsewhere on the board
/COAG_CTRL: R3.2; also elsewhere on the board
/CUT_CTRL: R2.2; also elsewhere on the board
/GEN_COAG: U3.4; also elsewhere on the board
/GEN_CUT: U2.4; also elsewhere on the board
/GEN_LIGA: U5.4; also elsewhere on the board
/LIGA_CTRL: R5.2; also elsewhere on the board
/LIGA_GEN_COM: U5.3; also elsewhere on the board
/MONO_GEN_COM: U2.3, U3.3; also elsewhere on the board
GND: Q2.2, Q3.2, Q5.2, R6.1, R7.1, R9.1; also elsewhere on the board
unnamed: D2.2 (A), Q2.3, U2.8
unnamed: D3.2 (A), Q3.3, U3.8
unnamed: D5.2 (A), Q5.3, U5.8
unnamed: Q2.1, R2.1, R6.2
unnamed: Q3.1, R3.1, R7.2
unnamed: Q5.1, R5.1, R9.2
